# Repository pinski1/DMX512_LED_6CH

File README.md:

# DMX512 LED 6Ch
A DMX512 Controller for 6 LED channels

## uhm

Somewhat mimicing:
https://www.aliexpress.com/item/32795465472.html

should be buildable with JLC's SMT Assembly service.

This is kinda 4 hours work, minimal maths/thinking.

Needs a SMPS, the maths on the MOSFETs doing and a couple of cost reduction passes.

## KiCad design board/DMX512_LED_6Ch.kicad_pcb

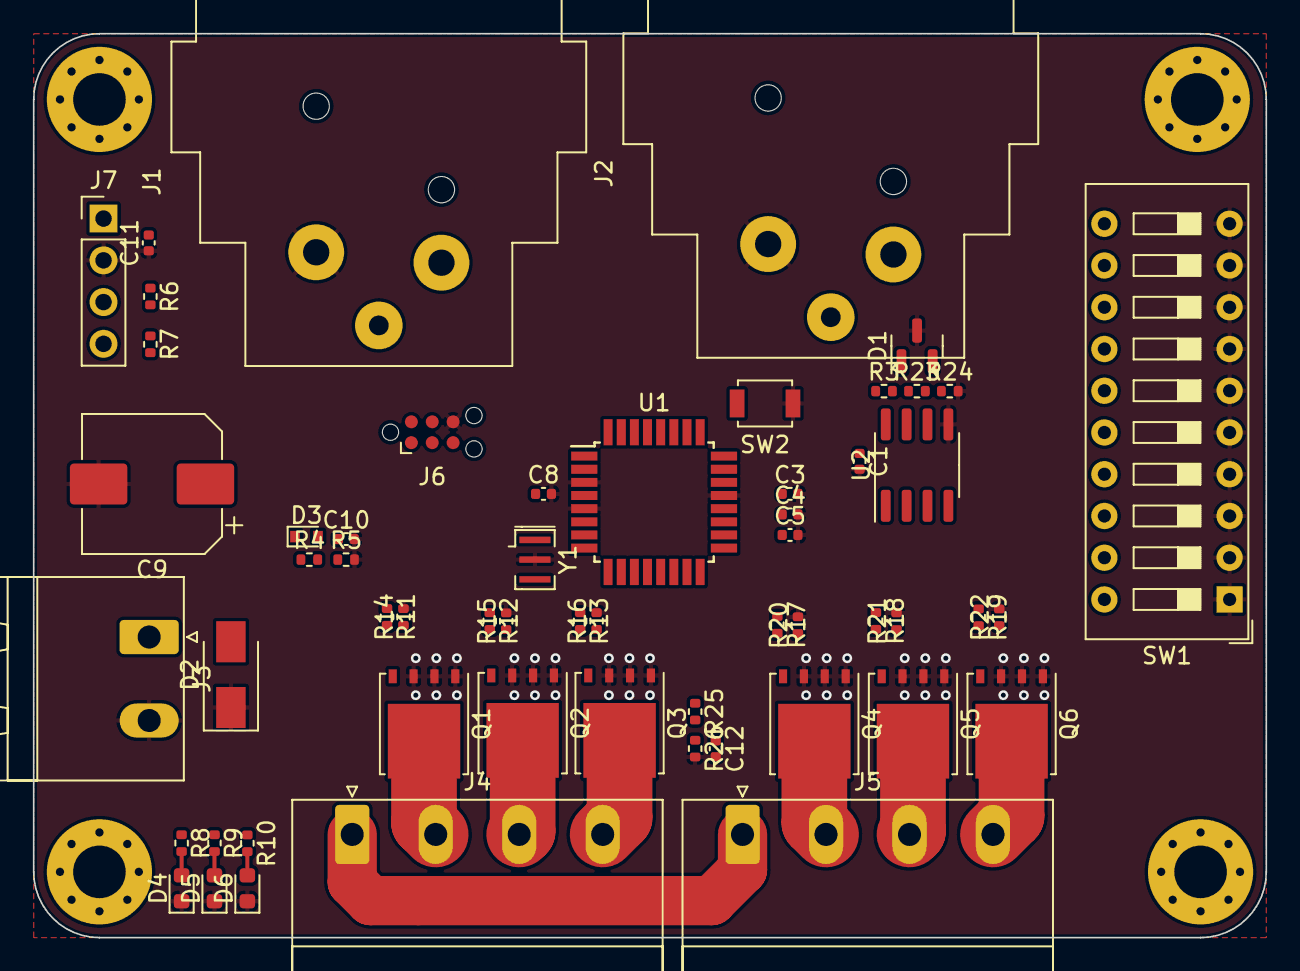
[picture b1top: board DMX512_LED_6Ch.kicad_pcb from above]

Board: 2 copper layers, 75.0 x 55.0 mm, 61 parts (0 on the bottom side), 37 nets.

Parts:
C1, C3, C4, C5, C8, C10, C11: 100nF; C_0402_1005Metric
C9: 47uF; CP_Elec_8x10
C12: 1uF; C_0402_1005Metric
D1: NUP2105L; SOT-23
D2: D_TVS; D_SMA
D3: RB751V-40WS RRG; D_SOD-523
D4, D5, D6: LED; LED_0603_1608Metric
H1, H2, H3, H4: MountingHole; MountingHole_3.2mm_M3_Pad_Via
J1, J2: XLR3; Jack_XLR_Neutrik_NC3FAAH-0_Horizontal
J3: Conn_01x02; PhoenixContact_MSTBA_2,5_2-G-5,08_1x02_P5.08mm_Horizontal
J4, J5: Conn_01x04; PhoenixContact_MSTBA_2,5_4-G-5,08_1x04_P5.08mm_Horizontal
J6: AVR-ISP-6; Tag-Connect_TC2030-IDC-NL_2x03_P1.27mm_Vertical
J7: Conn_01x04; PinHeader_1x04_P2.54mm_Vertical
Q1, Q2, Q3, Q4, Q5, Q6: BSC028N06LS3; TDSON-8-1
R3, R24: 562; R_0402_1005Metric
R4: 130k; R_0402_1005Metric
R5: 16k; R_0402_1005Metric
R6, R7: 2k2; R_0402_1005Metric
R8, R9, R10: 1k; R_0402_1005Metric
R11, R12, R13, R17, R18, R19: 10R; R_0402_1005Metric
R14, R15, R16, R20, R21, R22, R25, R26: 10k; R_0402_1005Metric
R23: 133; R_0402_1005Metric
SW1: SW_DIP_x10; SW_DIP_SPSTx10_Slide_9.78x27.58mm_W7.62mm_P2.54mm
SW2: SW_Push; SW_SPST_B3U-1000P
U1: ATmega8A-A; TQFP-32_7x7mm_P0.8mm
U2: MAX485E; SOIC-8_3.9x4.9mm_P1.27mm
Y1: 16MHz; Resonator_SMD_Murata_CSTxExxV-3Pin_3.0x1.1mm

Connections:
+3V3: C11.2, D3.1 (K), J7.1, R25.1
+5V: C1.1, C3.1, C4.1, C5.1, C8.1, J6.2 (VCC), R3.1, R6.1, R7.1, U1.4 (VCC), U1.6 (VCC), U1.18 (AVCC), U2.8 (VCC)
/CH1_BLU_EN: R13.1, U1.10 (PD6)
/CH1_GRN_EN: R12.1, U1.9 (PD5)
/CH1_RED_EN: R11.1, U1.1 (PD3)
/COMS/DATA1_N: D1.2 (K), J1.2, J2.2, R23.2, R24.1, U2.6 (A)
/COMS/DATA1_P: D1.1 (K), J1.3, J2.3, R3.2, R23.1, U2.7 (B)
/DMX_DIR: U1.32 (PD2), U2.2 (~RE), U2.3 (DE)
/DMX_IN: U1.30 (PD0), U2.1 (RO)
/DMX_OUT: U1.31 (PD1), U2.4 (DI)
/I2C_SCL: J7.4, R7.2, U1.28 (PC5)
/I2C_SDA: J7.3, R6.2, U1.27 (PC4)
/MISO: J6.1 (MISO), U1.16 (PB4)
/MOSI: J6.4 (MOSI), U1.15 (PB3)
/SCK: J6.3 (SCK), U1.17 (PB5)
/TMP_MON: C12.1, R25.2, R26.1, U1.19 (ADC6)
/VCC_MON: C10.1, D3.2 (A), R4.2, R5.1, U1.22 (ADC7)
/~RESET: J6.5 (~RST), SW2.2, U1.29 (PC6/~RESET)
GND: C1.2, C3.2, C4.2, C5.2, C8.2, C9.2, C10.2, C11.1, C12.2, D1.3 (A), D2.1 (A1), D4.1 (K), D5.1 (K), D6.1 (K), J1.1, J2.1, J3.2, J6.6 (GND), J7.2, Q1.1 (S), Q1.2 (S), Q1.3 (S), Q2.1 (S), Q2.2 (S), Q2.3 (S), Q3.1 (S), Q3.2 (S), Q3.3 (S), Q4.1 (S), Q4.2 (S), Q4.3 (S), Q5.1 (S), Q5.2 (S), Q5.3 (S), Q6.1 (S), Q6.2 (S), Q6.3 (S), R5.2, R14.2, R15.2, R16.2, R20.2, R21.2, R22.2, R24.2, R26.2, SW1.1, SW1.2, SW1.3, SW1.4, SW1.5, SW1.6, SW1.7, SW1.8, SW1.9, SW1.10, SW2.1, U1.3 (GND), U1.5 (GND), U1.21 (AGND), U2.5 (GND), Y1.2
unnamed: D4.2 (A), R8.2
unnamed: D5.2 (A), R9.2
unnamed: D6.2 (A), R10.2
unnamed: J4.2, Q1.5 (D)
unnamed: J4.3, Q2.5 (D)
unnamed: J4.4, Q3.5 (D)
unnamed: J5.2, Q4.5 (D)
unnamed: J5.3, Q5.5 (D)
unnamed: J5.4, Q6.5 (D)
unnamed: Q1.4 (G), R11.2, R14.1
unnamed: Q2.4 (G), R12.2, R15.1
unnamed: Q3.4 (G), R13.2, R16.1
unnamed: Q4.4 (G), R17.2, R20.1
unnamed: Q5.4 (G), R18.2, R21.1
unnamed: Q6.4 (G), R19.2, R22.1
unnamed: U1.7 (PB6/XTAL1), Y1.1
unnamed: U1.8 (PB7/XTAL2), Y1.3
VCC: C9.1, D2.2 (A2), J3.1, J4.1, J5.1, R4.1

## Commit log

2022-01-03 inital commit
2022-01-03 adding KiCad v6.0 project
2022-01-03 adding latest schematic
2022-01-03 doing some cost reduction
